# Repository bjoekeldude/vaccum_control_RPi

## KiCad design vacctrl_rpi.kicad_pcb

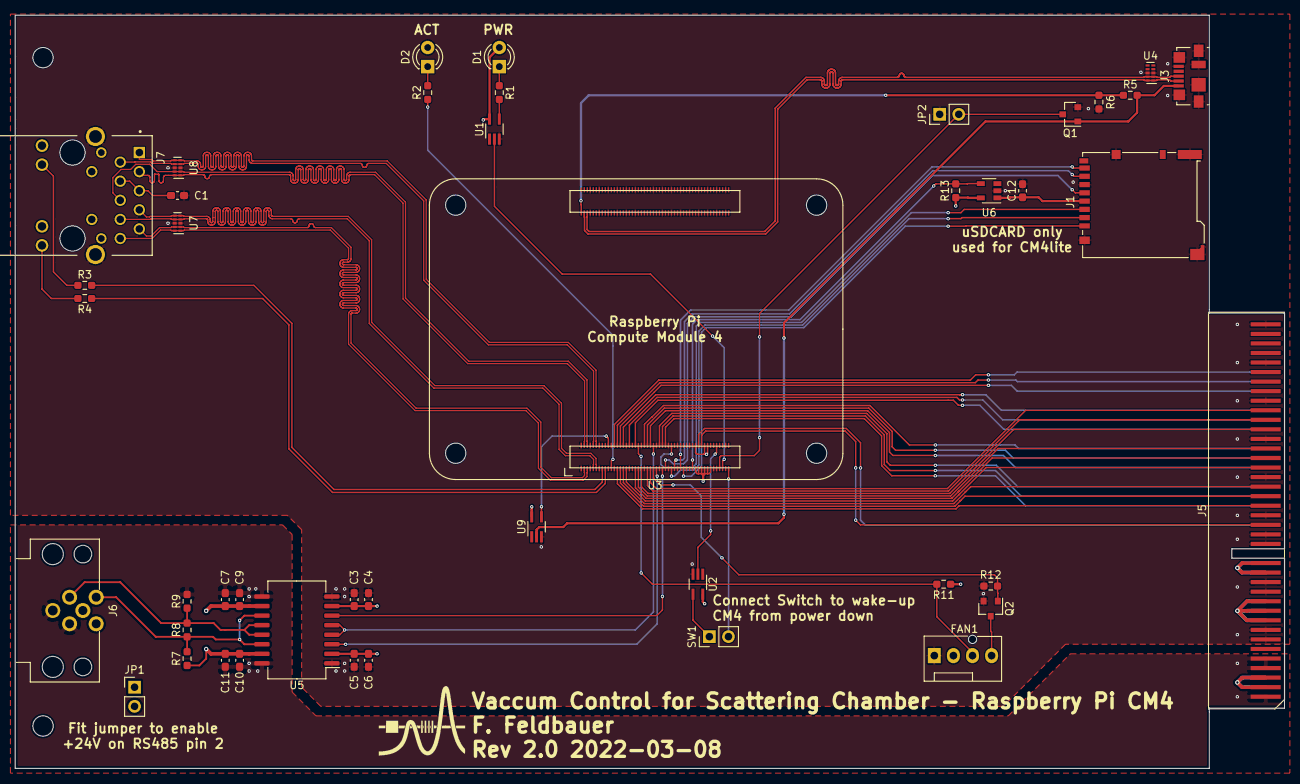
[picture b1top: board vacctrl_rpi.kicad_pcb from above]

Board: 4 copper layers, 168.8 x 100.2 mm, 47 parts (0 on the bottom side), 73 nets.

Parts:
C1, C3, C6, C9, C11: 100n; C_0603_1608Metric_Pad1.08x0.95mm_HandSolder
C4, C7: 10n; C_0603_1608Metric_Pad1.08x0.95mm_HandSolder
C5, C10: 10u; C_0603_1608Metric_Pad1.08x0.95mm_HandSolder
C12: 10u; C_0603_1608Metric_Pad1.05x0.95mm_HandSolder
D1: LED Red; LED_D3.0mm
D2: LED Green; LED_D3.0mm
FAN1: Fan_4pin; FanPinHeader_1x04_P2.54mm_Vertical
G1: PALUMA-logo; PALUMA-Logo
H1, H2: MountingHole; MountingHole_2.7mm_M2.5_DIN965
J1: Micro_SD_Card_Det; microSD_HC_Hirose_DM3BT-DSF-PEJS
J3: USB_OTG; USB_Micro-B_Molex_47346-0001
J5: Samtec_MECF-40-Polarized_Edge; Samtec_MECF-40-0_-L-DV_2x40_P1.27mm_Polarized_Edge
J6: M12_5A; CONEC_43-01198
J7: A70-112-331N126; EDAC_A70-112-331N126
JP1: Jumper_NC_Small; PinHeader_1x02_P2.54mm_Vertical
JP2: dnp; PinHeader_1x02_P2.54mm_Vertical
Q1, Q2: BSS138; SOT-23
R1, R2: 1k; R_0603_1608Metric_Pad0.98x0.95mm_HandSolder
R3, R4: 470R; R_0603_1608Metric_Pad0.98x0.95mm_HandSolder
R5, R6: 2k2 1%; R_0603_1608Metric_Pad0.98x0.95mm_HandSolder
R7, R9: 680R; R_0603_1608Metric_Pad0.98x0.95mm_HandSolder
R8: 100R; R_0603_1608Metric_Pad0.98x0.95mm_HandSolder
R11: 36k; R_0603_1608Metric_Pad0.98x0.95mm_HandSolder
R12: 10k; R_0603_1608Metric_Pad0.98x0.95mm_HandSolder
R13: 12k 1%; R_0603_1608Metric_Pad0.98x0.95mm_HandSolder
SW1: SW_Push; PinHeader_1x02_P2.54mm_Vertical
U1, U2, U9: 74LVC1G07SE-7; SOT-353_SC-70-5_Handsoldering
U3: Raspi_CM4; raspi-cm4
U4, U7, U8: TPD4EUSB30; USON-10_2.5x1.0mm_P0.5mm
U5: ADM2682E; SOIC-16W_7.5x12.8mm_P1.27mm
U6: AP2171W; SOT-23-5

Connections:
+3V3: C3.1, C4.1, C5.1, C6.1, D1.2, D2.2, J5.27, J5.28, J5.29, J5.30, J7.15, J7.17, R11.1, R13.1, U1.5, U3.78, U3.84, U3.86, U5.2, U5.7, U6.5
+5V: FAN1.2, J5.17, J5.18, J5.19, J5.20, J5.21, J5.22, U2.5, U3.77, U3.79, U3.81, U3.83, U3.85, U3.87, U9.5
+24V: J5.3, J5.4, J5.5, J5.6, JP1.2
/Backplane IF/SCL: J5.38, U3.80
/Backplane IF/SDA: J5.37, U3.82
/Ethernet IF/ETH_0_N: J7.2, U3.10, U8.4, U8.7
/Ethernet IF/ETH_0_P: J7.1, U3.12, U8.5, U8.6
/Ethernet IF/ETH_1_N: J7.6, U3.6, U8.2, U8.9
/Ethernet IF/ETH_1_P: J7.3, U3.4, U8.1, U8.10
/Ethernet IF/ETH_2_N: J7.8, U3.9, U7.4, U7.7
/Ethernet IF/ETH_2_P: J7.7, U3.11, U7.5, U7.6
/Ethernet IF/ETH_3_N: J7.10, U3.5, U7.1, U7.10
/Ethernet IF/ETH_3_P: J7.9, U3.3, U7.2, U7.9
/Ethernet IF/ETH_LEDG: R3.2, U3.15
/Ethernet IF/ETH_LEDY: R4.1, U3.17
/RS485 IF/RS485-D+: J6.1, R7.2, R8.1, U5.11, U5.14
/RS485 IF/RS485-D-: J6.4, R8.2, R9.1, U5.12, U5.13
/RS485 IF/VISO: C7.1, C9.1, C10.1, C11.1, R7.1, U5.10, U5.15
/RS485 IF/uart_rts: U3.50, U5.4, U5.5
/RS485 IF/uart_rx: U3.51, U5.3
/RS485 IF/uart_tx: U3.55, U5.6
/Raspi_CM4_GPIO/EEPROM_nWP: U3.20, U9.4
/Raspi_CM4_GPIO/GLOBAL_EN: SW1.2, U3.99
/Raspi_CM4_GPIO/GPIO02: J5.42, U3.58
/Raspi_CM4_GPIO/GPIO03: J5.44, U3.56
/Raspi_CM4_GPIO/GPIO04: J5.46, U3.54
/Raspi_CM4_GPIO/GPIO05: J5.60, U3.34
/Raspi_CM4_GPIO/GPIO06: J5.62, U3.30
/Raspi_CM4_GPIO/GPIO07: J5.51, U3.37
/Raspi_CM4_GPIO/GPIO08: J5.53, U3.39
/Raspi_CM4_GPIO/GPIO10: J5.54, U3.44
/Raspi_CM4_GPIO/GPIO11: J5.58, U3.38
/Raspi_CM4_GPIO/GPIO12: J5.49, U3.31
/Raspi_CM4_GPIO/GPIO13: J5.66, U3.28
/Raspi_CM4_GPIO/GPIO16: J5.45, U3.29
/Raspi_CM4_GPIO/GPIO19: J5.68, U3.26
/Raspi_CM4_GPIO/GPIO20: J5.43, U3.27
/Raspi_CM4_GPIO/GPIO21: J5.41, U3.25
/Raspi_CM4_GPIO/GPIO22: J5.52, U3.46
/Raspi_CM4_GPIO/GPIO23: J5.61, U3.47
/Raspi_CM4_GPIO/GPIO24: J5.59, U3.45
/Raspi_CM4_GPIO/GPIO25: J5.57, U3.41
/Raspi_CM4_GPIO/GPIO26: J5.70, U3.24
/Raspi_CM4_GPIO/GPIO27: J5.50, U3.48
/Raspi_CM4_GPIO/Pi_nLED_Activity: R2.1, U3.21
/Raspi_CM4_GPIO/RUN_PG: U2.2, U3.92
/Raspi_CM4_GPIO/SD_CLK: J1.5, U3.57
/Raspi_CM4_GPIO/SD_CMD: J1.3, U3.62
/Raspi_CM4_GPIO/SD_DAT0: J1.7, U3.63
/Raspi_CM4_GPIO/SD_DAT1: J1.8, U3.67
/Raspi_CM4_GPIO/SD_DAT2: J1.1, U3.69
/Raspi_CM4_GPIO/SD_DAT3: J1.2, U3.61
/Raspi_CM4_GPIO/SD_PWR: C12.1, J1.4, U6.1
/Raspi_CM4_GPIO/SD_PWR_ON: R13.2, U3.75, U6.4
/Raspi_CM4_GPIO/USB_VBUS: J3.1, Q1.1, R5.2, U9.2
/Raspi_CM4_GPIO/nPWR_LED: U1.2, U3.95
/Raspi_CM4_GPIO/nRPIBOOT: JP2.2, Q1.3, U3.93
/Raspi_CM4_GPIO/tacho: FAN1.3, R11.2, U3.40
/Raspi_CM4_GPIO/~pwm: Q2.1, R12.1, U3.49
/Raspi_CM4_HighSpeed/USB_N: J3.2, U3.103, U4.1, U4.10
/Raspi_CM4_HighSpeed/USB_OTG: R5.1, R6.2, U3.101
/Raspi_CM4_HighSpeed/USB_P: J3.3, U3.105, U4.2, U4.9
GND: C1.1, C3.2, C4.2, C5.2, C6.2, C12.2, FAN1.1, J1.6, J1.11, J3.5, J3.6, J5.13, J5.14, J5.15, J5.16, J5.23, J5.24, J5.25, J5.26, J5.33, J5.34, J5.35, J5.36, J5.39, J5.40, J5.47, J5.48, J5.55, J5.56, J5.63, J5.64, J5.71, J5.72, J5.79, J5.80, J7.S1, J7.S2, JP2.1, Q1.2, Q2.2, R6.1, R12.2, U1.3, U2.3, U3.1, U3.2, U3.7, U3.8, U3.13, U3.14, U3.22, U3.23, U3.32, U3.33, U3.42, U3.43, U3.52, U3.53, U3.59, U3.60, U3.65, U3.66, U3.71, U3.74, U3.89, U3.91, U3.98, U3.107, U3.108, U3.113, U3.114, U3.119, U3.120, U3.125, U3.126, U3.131, U3.132, U3.137, U3.138, U3.144, U3.150, U3.155, U3.156, U3.161, U3.162, U3.167, U3.168, U3.173, U3.174, U3.179, U3.180, U3.185, U3.186, U3.191, U3.192, U3.197, U3.198, U4.3, U4.8, U5.1, U5.8, U6.2, U7.3, U7.8, U8.3, U8.8, U9.3
GND1: C7.2, C9.2, C10.2, C11.2, J5.1, J5.2, J5.7, J5.8, J5.9, J5.10, J6.3, J6.S, R9.2, U5.9, U5.16
unnamed: C1.2, J7.4, J7.5
unnamed: D1.1, R1.1
unnamed: D2.1, R2.2
unnamed: FAN1.4, Q2.3
unnamed: J6.2, JP1.1
unnamed: J7.16, R3.1
unnamed: J7.18, R4.2
unnamed: R1.2, U1.4
unnamed: SW1.1, U2.4
